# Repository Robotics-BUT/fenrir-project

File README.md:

# Fenrir Project - Universal Robotic Platform

The Fenrir Project is an open source of a multi purpose education robot dedicated for wide range of applications and usage in high-schools and universities.

The robot is based on Raspberry Pi 4 and Arduino Nano. The Raspberry Pi provides computational power, ROS2 support, WiFi connection and USB support. The Arduino Nano extends the PRi IOs and handles peripherals.

The development is currently still under development

## Robot Overview

### Robot visualization 

### Overview schematic

### Power supply schematic

### Wiring Overview

**Note**: The sensors numbering goes from left to right
 - Ultrasound 1 - left, Ultrasound 2 - center, Ultrasound 3 - right
 - Line sensor 1 - left, Line sensor 2 - right
 - Motor 1 - left, Motor 2 - right
 - Encoder 1 - left, Encoder 2 - right

| **Module A**       | **Pin**  | **Module B**        | **Pin**        | **Type**              | **Length** | **Note** |
|--------------------|----------|---------------------|----------------|-----------------------|------------|----------|
| Battery 1          | -        | PD Module           | -              | USB-C - USB-C         | 15cm       | -        |
| Battery 2          | -        | Raspberry Pi        | -              | USB-C - USB-C         | 15cm       | -        |
| Raspberry Pi       | -        | Camera              | -              | CSI Cable             | 10cm       | -        |
| Raspberry Pi       | 3v3      | GPS                 | VCC            | wire (blue)           | 10cm       | 3V3      |
| Raspberry Pi       | GND      | GPS                 | GND            | wire (black)          | 10cm       | GND      |
| Raspberry Pi       | Rx       | GPS                 | TxD            | wire (purple)         | 10cm       | UART     |
| Raspberry Pi       | 5V       | I2C Board           | 5V             | wire (red)            | 8cm        | 5V       |
| Raspberry Pi       | GND      | I2C Board           | GND            | wire (black)          | 8cm        | GND      |
| Raspberry Pi       | SCL      | I2C Board           | SCL            | wire (yellow)         | 8cm        | SCL      |
| Raspberry Pi       | SDA      | I2C Board           | SDA            | wire (green)          | 8cm        | SDA      |
| Raspberry Pi       | -        | LIDAR               | -              | USB-A - microUSB      | 10cm       | -        |
| I2C Board          | 5V       | LCD                 | VCC            | wire (red)            | 8cm        | 5V       |
| I2C Board          | GND      | LCD                 | GND            | wire (black)          | 8cm        | GND      |
| I2C Board          | SCL      | LCD                 | SCL            | wire (yellow)         | 8cm        | SCL      |
| I2C Board          | SDA      | LCD                 | SDA            | wire (green)          | 8cm        | SDA      |
| I2C Board          | 5V       | Arduino             | VCC            | wire (red)            | 15cm       | 5V       |
| I2C Board          | GND      | Arduino             | GND            | wire (black)          | 15cm       | GND      |
| I2C Board          | SCL      | Arduino             | SCL            | wire (yellow)         | 15cm       | SCL      |
| I2C Board          | SDA      | Arduino             | SDA            | wire (green)          | 15cm       | SDA      |
| Arduino            | US1      | Ultrasound 1        | Vcc            | wire (red)            | 10cm       | 5V       |
| Arduino            | US1      | Ultrasound 1        | GND            | wire (black)          | 10cm       | GND      |
| Arduino            | US1      | Ultrasound 1        | Echo/Trig      | wire (blue)           | 10cm       | signal   |
| Arduino            | US2      | Ultrasound 2        | Vcc            | wire (red)            | 10cm       | 5V       |
| Arduino            | US2      | Ultrasound 2        | GND            | wire (black)          | 10cm       | GND      |
| Arduino            | US2      | Ultrasound 2        | Echo/Trig      | wire (blue)           | 10cm       | signal   |
| Arduino            | US3      | Ultrasound 3        | Vcc            | wire (red)            | 15cm       | 5V       |
| Arduino            | US3      | Ultrasound 3        | GND            | wire (black)          | 15cm       | GND      |
| Arduino            | US3      | Ultrasound 3        | Echo/Trig      | wire (blue)           | 15cm       | signal   |
| Arduino            | Line1    | Line Sens. 1        | VCC            | wire (red)            | 15cm       | 5V       |
| Arduino            | Line1    | Line Sens. 1        | GND            | wire (black)          | 15cm       | GND      |
| Arduino            | Line1    | Line Sens. 1        | A0             | wire (blue)           | 15cm       | signal   |
| Arduino            | Line2    | Line Sens. 2        | VCC            | wire (red)            | 15cm       | 5V       |
| Arduino            | Line2    | Line Sens. 2        | GND            | wire (black)          | 15cm       | GND      |
| Arduino            | Line2    | Line Sens. 2        | A0             | wire (blue)           | 15cm       | signal   |
| Arduino            | 5V       | Encoder 1           | -              | wire (yellow)         | 20cm       | 5V       |
| Arduino            | GND      | Encoder 1           | -              | wire (brown)          | 20cm       | GND      |
| Arduino            | EN1A     | Encoder 1           | -              | wire (red)            | 20cm       | A        |
| Arduino            | EN1B     | Encoder 1           | -              | wire (orange)         | 20cm       | B        |
| Arduino            | 5V       | Encoder 2           | -              | wire (yellow)         | 20cm       | 5V       |
| Arduino            | GND      | Encoder 2           | -              | wire (brown)          | 20cm       | GND      |
| Arduino            | EN2A     | Encoder 2           | -              | wire (red)            | 20cm       | A        |
| Arduino            | EN2B     | Encoder 2           | -              | wire (orange)         | 20cm       | B        |
| Arduino            | GND      | PD Module           | OUT-           | wire (black)          | -          | -        |
| Arduino            | M1A      | H-Bridge            | IN3            | wire (yellow)         | 20cm       | PWM A+   |
| Arduino            | M1B      | H-Bridge            | IN4            | wire (green)          | 20cm       | PWM A-   |
| Arduino            | M2A      | H-Bridge            | IN1            | wire (yellow)         | 20cm       | PWM B+   |
| Arduino            | M2B      | H-Bridge            | IN2            | wire (green)          | 20cm       | PWM B-   |
| PD Module          | +        | H-Bridge            | +12V           | wire (orange)         | 15cm       | 12V      |
| PD Module          | -        | H-Bridge            | GND            | wire (black)          | 15cm       | GND      |
| H-Bridge           | OUT1+    | Motor 1             | -              | wire (green)          | 20cm       | +        |
| H-Bridge           | OUT1-    | Motor 1             | -              | wire (blue)           | 20cm       | -        |
| H-Bridge           | OUT2+    | Motor 2             | -              | wire (green)          | 20cm       | +        |
| H-Bridge           | OUT2-    | Motor 2             | -              | wire (blue)           | 20cm       | -        |

## Equipment

| Role                   | Component           | URL                                                                                                                                                                                                                                                                                             |
|------------------------|---------------------|-------------------------------------------------------------------------------------------------------------------------------------------------------------------------------------------------------------------------------------------------------------------------------------------------|
| Main Computer          | RPi                 | [link](https://cz.mouser.com/ProductDetail/Raspberry-Pi/SC01959?qs=T%252BzbugeAwjhNCW2QVhlotw%3D%3D)                                                                                                                                                                                            |
| Helper Microcontroller | Arduino Nano        | [link](https://www.laskakit.cz/arduino-nano-r3--atmega328p-klon--pripajene-piny/)                                                                                                                                                                                                               |
| 2x Battery             | Powerbank 10000 mAh | [link](https://www.alza.cz/alzapower-parade-power-delivery?dq=7177723)                                                                                                                                                                                                                          |
| Camera                 | RPi Camera v2       | [link](https://rpishop.cz/mipi-kamerove-moduly/329-raspberry-pi-kamera-modul-v2.html?utm_source=google&utm_medium=cpc&utm_campaign=CZ-PMax-Raspberry%20Pi&utm_id=19691368073&gad_source=1&gclid=Cj0KCQiAr7C6BhDRARIsAOUKifiiX4p72F4J8UeeA5uyoK2IDEEryKLRjE0e5gLhURTCTTf2cGW-ZpQaAr76EALw_wcB)   |
| GPS                    | NEO-7M module       | [link](https://dratek.cz/arduino/1733-gps-satelitni-urceni-polohy-neo-7m-modul.html?_gl=1*16f2vtr*_up*MQ..*_gs*MQ..&gclid=Cj0KCQiAr7C6BhDRARIsAOUKifhd7u9T5IjiCyc4w0n-WqehlzG5F2pNwJ4JP5M_eQDHW-daU_NkSKYaAn-_EALw_wcB)                                                                         |
| 2D LiDAR               | RPLiDAR A1M8        | [link](https://rpishop.cz/lidary/1631-rplidar-a1m8-360stupnovy-laserovy-scanner-kit-dosah-12m.html)                                                                                                                                                                                             |
| LCD                    | HD44780 20x4 I2C    | [link](https://dratek.cz/arduino/1421-eses-i2c-20x4-display-pro-jednodeskove-pocitace.html?_gl=1*16f2vtr*_up*MQ..*_gs*MQ..&gclid=Cj0KCQiAr7C6BhDRARIsAOUKifhd7u9T5IjiCyc4w0n-WqehlzG5F2pNwJ4JP5M_eQDHW-daU_NkSKYaAn-_EALw_wcB)                                                                  |
| 3x Ultrasound          | SRF-05              | [link](https://dratek.cz/arduino/1735-meric-vzdalenosti-ultrazvukovy-5pin-hy-srf05-pro-arduino.html?gad_source=1&gclid=Cj0KCQiAr7C6BhDRARIsAOUKifhd7u9T5IjiCyc4w0n-WqehlzG5F2pNwJ4JP5M_eQDHW-daU_NkSKYaAn-_EALw_wcB)                                                                            |
| 2x Line Sensor         | TCRT5000 module     | [link](https://www.laskakit.cz/arduino-infracerveny-senzor-sledovani-cary-s-lm393/)                                                                                                                                                                                                             |
| H Bridge               | L298N module        | [link](https://www.laskakit.cz/h-mustek-pro-krokovy-motor-l298n--dualni-motorovy-modul/)                                                                                                                                                                                                        |
| Motor with Encoder     | DG01D‐E             | [link](https://cz.mouser.com/ProductDetail/SparkFun/ROB-16413?qs=vmHwEFxEFR%2F20T1Ah9zr5w%3D%3D)                                                                                                                                                                                                |
| IMU                    | MPU6050             | [link](https://pajenicko.cz/gyroskop-akcelerometr-gy-521-s-mpu6050-i2c)                                                                                                                                                                                                                         |
| Barometer              | BME280              | [link](https://pajenicko.cz/senzor-na-mereni-teploty-vlhkosti-tlaku-bme280)                                                                                                                                                                                                                     |
| Real Time Clock        | DS3231              | [link](https://www.laskakit.cz/arduino-rtc-hodiny-realneho-casu-ds3231-at24c32/?utm_source=google&utm_medium=cpc&utm_campaign=1_PMax_%5BCZ%5D_Top_tROAS_540&utm_id=18587021915&gad_source=1&gclid=Cj0KCQiAr7C6BhDRARIsAOUKifg6UUgWdBpultpbW-joaJkbae34LBj8l6PJlVsHSvLgqnOoyetU0BsaAva-EALw_wcB) |
| ADC                    | ADS1115             | [link](https://pajenicko.cz/ad-prevodnik-ads1115-s-programovatelnym-zesilenim-16bit-4-kanaly-i2c-rozhrani)                                                                                                                                                                                      |
| UWB (not yet)          | DWM1000             | [link](https://www.laskakit.cz/decawave-dwm1000-lokalizacni-modul/)                                                                                                                                                                                                                             |
| DC/DC Step Up          | XL6009              | [link](https://www.laskakit.cz/step-up-boost-menic-s-xl6009--cervena/)                                                                                                                                                                                                                          |
| Power Delivery         | USB-C PD module     | [link](https://www.laskakit.cz/usb-c-pd-qc-prepinac-napajeciho-napeti/?utm_source=google&utm_medium=cpc&utm_campaign=1_PMax_%5BCZ%5D_Rest_tROAS_540&utm_id=20484705754&gad_source=1&gclid=Cj0KCQiAr7C6BhDRARIsAOUKifjczsmkcfvSqKLF3lqhT2G3EaCcH9kkrkxwS225di7C_nkNrmd77JoaAueFEALw_wcB)         |
| Switch                 |                     | [link](https://pajenicko.cz/kulaty-kolebkovy-spinac-se-zelenou-led-12v-20a)                                                                                                                                                                                                                     |

## Simulation

A Gazebo simulator of Fenrir lives in [`simulation/`](./simulation). It is a
digital twin of the robot: it exposes the same `/bpc_prp_robot/*` ROS 2 topics
as the real hardware, so course code runs unchanged in simulation and on the
robot.

It runs in a Docker container — no native Gazebo install needed. The line and
corridor worlds are ready; the maze world is in progress. See
[`simulation/README.md`](./simulation/README.md) for setup and how to run it.

## Acknowledgments

This work was created with the support of project RP182401001 under the PPSŘ 2025 program.

## Authors

Adam Ligocki - adam.ligocki@vut.cz

Petr Šopák - petr.sopak@vut.cz

Jakum Minařík

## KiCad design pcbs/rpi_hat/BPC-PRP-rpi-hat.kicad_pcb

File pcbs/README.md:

# Fenrir Project - PCBs

### RPi Ext Board

Schema

Render Top

Render Bot

### Arduino Board

Schema

Render Top

### I2C Board

Schema

Render Top

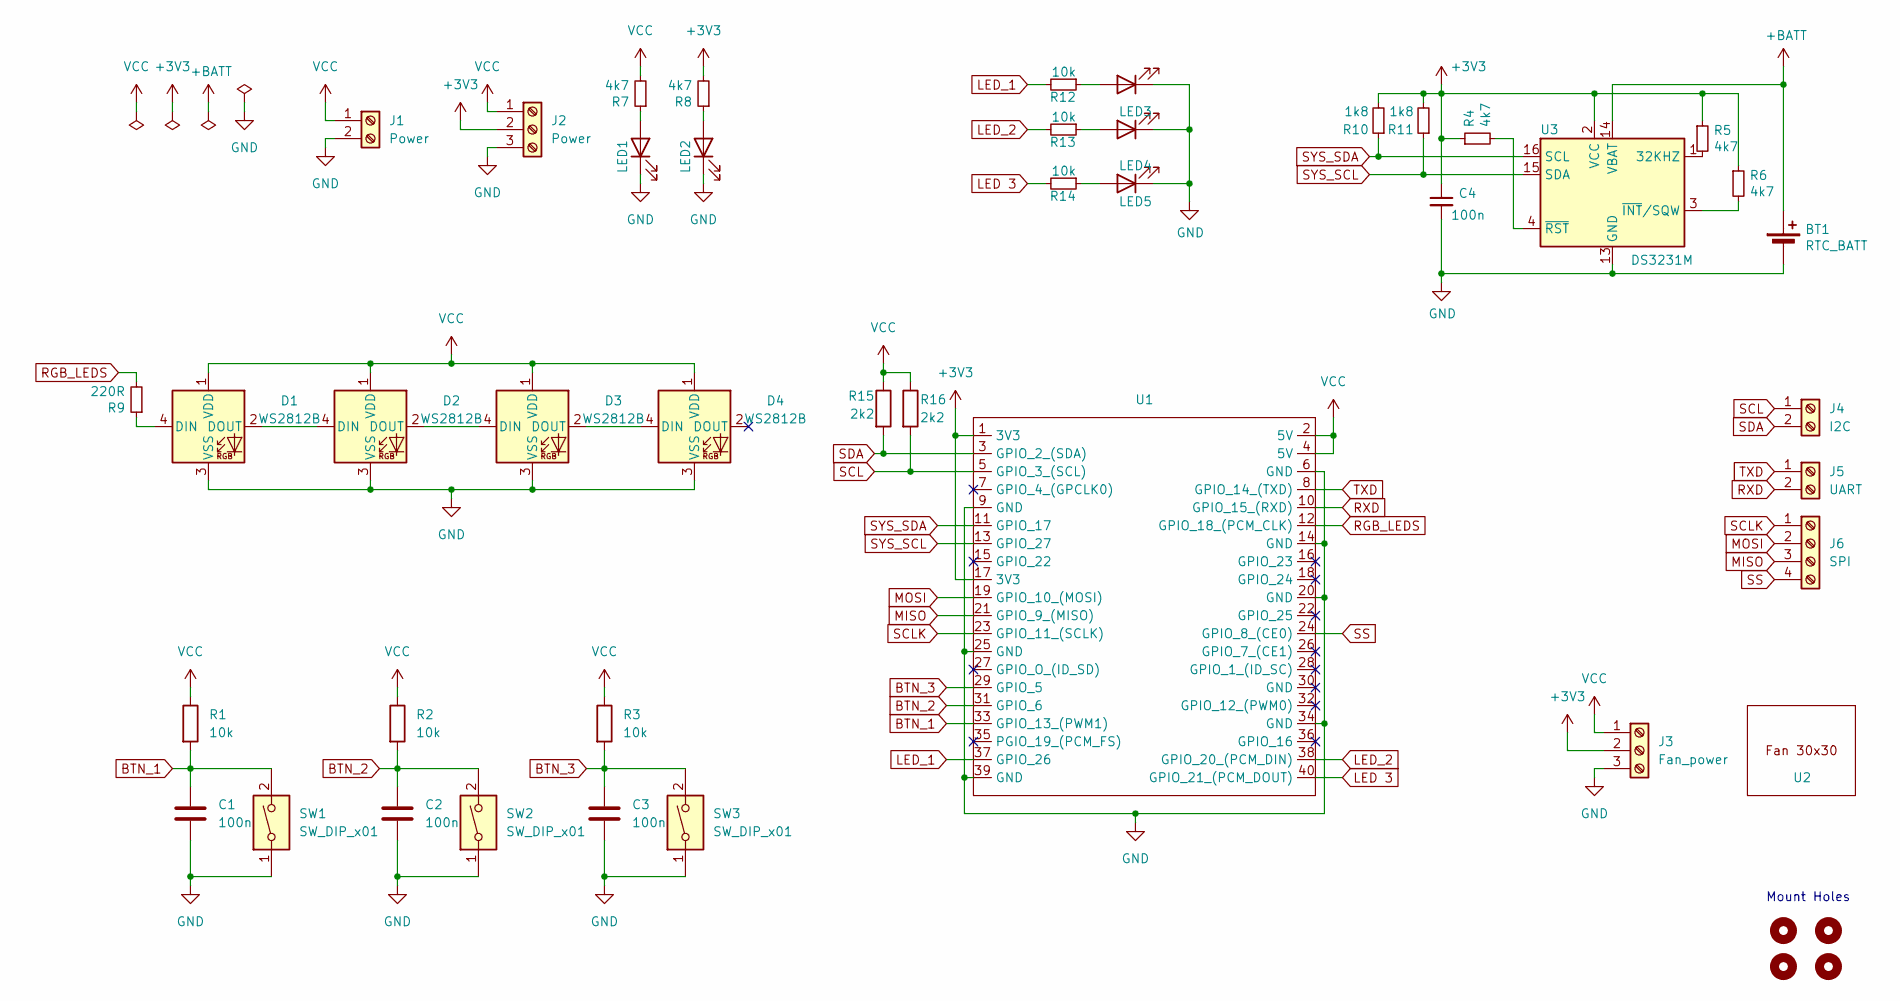
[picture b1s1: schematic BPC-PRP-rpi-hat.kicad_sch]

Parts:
BT1: RTC_BATT; BatteryHolder_Keystone_3000_1x12mm
C1, C2, C3, C4: 100n; C_1206_3216Metric
D1, D2, D3, D4: WS2812B; LED_WS2812B_PLCC4_5.0x5.0mm_P3.2mm
H1, H2, H3, H4: MountingHole; MountingHole_3.2mm_M3
J1: Power; TerminalBlock_RND_205-00001_1x02_P5.00mm_Horizontal
J2: Power; TerminalBlock_TE_282834-3_1x03_P2.54mm_Horizontal
J3: Fan_power; TerminalBlock_TE_282834-3_1x03_P2.54mm_Horizontal
J4: I2C; TerminalBlock_TE_282834-2_1x02_P2.54mm_Horizontal
J5: UART; TerminalBlock_TE_282834-2_1x02_P2.54mm_Horizontal
J6: SPI; TerminalBlock_TE_282834-4_1x04_P2.54mm_Horizontal
LED1, LED2, LED3, LED4, LED5: LED_1206_3216Metric
R1, R2, R3, R12, R13, R14: 10k; R_1206_3216Metric
R4, R5, R6, R7, R8: 4k7; R_1206_3216Metric
R9: 220R; R_1206_3216Metric
R10, R11: 1k8; R_1206_3216Metric
R15, R16: 2k2; R_1206_3216Metric
SW1, SW2, SW3: SW_DIP_x01; SW_PUSH_6mm_H5mm
U1: PinSocket_2x20_P2.54mm_Vertical
U2: FAN_30
U3: DS3231M; SOIC-16W_7.5x10.3mm_P1.27mm

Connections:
+3V3: C4.1, J2.2, J3.2, R4.1, R5.1, R6.1, R8.2, R10.2, R11.2, U1.1 (3V3), U1.17 (3V3), U3.2 (VCC)
+BATT: BT1.1 (+), U3.14 (VBAT)
BTN_1: C1.1, R1.2, SW1.2, U1.33 (GPIO_13_(PWM1))
BTN_2: C2.1, R2.2, SW2.2, U1.31 (GPIO_6)
BTN_3: C3.1, R3.2, SW3.2, U1.29 (GPIO_5)
GND: BT1.2 (-), C1.2, C2.2, C3.2, C4.2, D1.3 (VSS), D2.3 (VSS), D3.3 (VSS), D4.3 (VSS), J1.2, J2.3, J3.3, LED1.1 (K), LED2.1 (K), LED3.1 (K), LED4.1 (K), LED5.1 (K), SW1.1, SW2.1, SW3.1, U1.6 (GND), U1.9 (GND), U1.14 (GND), U1.20 (GND), U1.25 (GND), U1.34 (GND), U1.39 (GND), U3.5 (GND), U3.6 (GND), U3.7 (GND), U3.8 (GND), U3.9 (GND), U3.10 (GND), U3.11 (GND), U3.12 (GND), U3.13 (GND)
LED 3: R14.2, U1.40 (GPIO_21_(PCM_DOUT))
LED_1: R12.2, U1.37 (GPIO_26)
LED_2: R13.2, U1.38 (GPIO_20_(PCM_DIN))
MISO: J6.3, U1.21 (GPIO_9_(MISO))
MOSI: J6.2, U1.19 (GPIO_10_(MOSI))
unnamed: D1.4 (DIN), R9.1
unnamed: D1.2 (DOUT), D2.4 (DIN)
unnamed: D2.2 (DOUT), D3.4 (DIN)
unnamed: D3.2 (DOUT), D4.4 (DIN)
unnamed: LED1.2 (A), R7.1
unnamed: LED2.2 (A), R8.1
unnamed: LED3.2 (A), R12.1
unnamed: LED4.2 (A), R13.1
unnamed: LED5.2 (A), R14.1
unnamed: R5.2, U3.1 (32KHZ)
unnamed: R6.2, U3.3 (~INT/SQW)
unnamed: R4.2, U3.4 (~RST)
RGB_LEDS: R9.2, U1.12 (GPIO_18_(PCM_CLK))
RXD: J5.2, U1.10 (GPIO_15_(RXD))
SCL: J4.1, R16.2, U1.5 (GPIO_3_(SCL))
SCLK: J6.1, U1.23 (GPIO_11_(SCLK))
SDA: J4.2, R15.2, U1.3 (GPIO_2_(SDA))
SS: J6.4, U1.24 (GPIO_8_(CE0))
SYS_SCL: R11.1, U1.13 (GPIO_27), U3.15 (SDA)
SYS_SDA: R10.1, U1.11 (GPIO_17), U3.16 (SCL)
TXD: J5.1, U1.8 (GPIO_14_(TXD))
VCC: D1.1 (VDD), D2.1 (VDD), D3.1 (VDD), D4.1 (VDD), J1.1, J2.1, J3.1, R1.1, R2.1, R3.1, R7.2, R15.1, R16.1, U1.2 (5V), U1.4 (5V)

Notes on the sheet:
Mount Holes

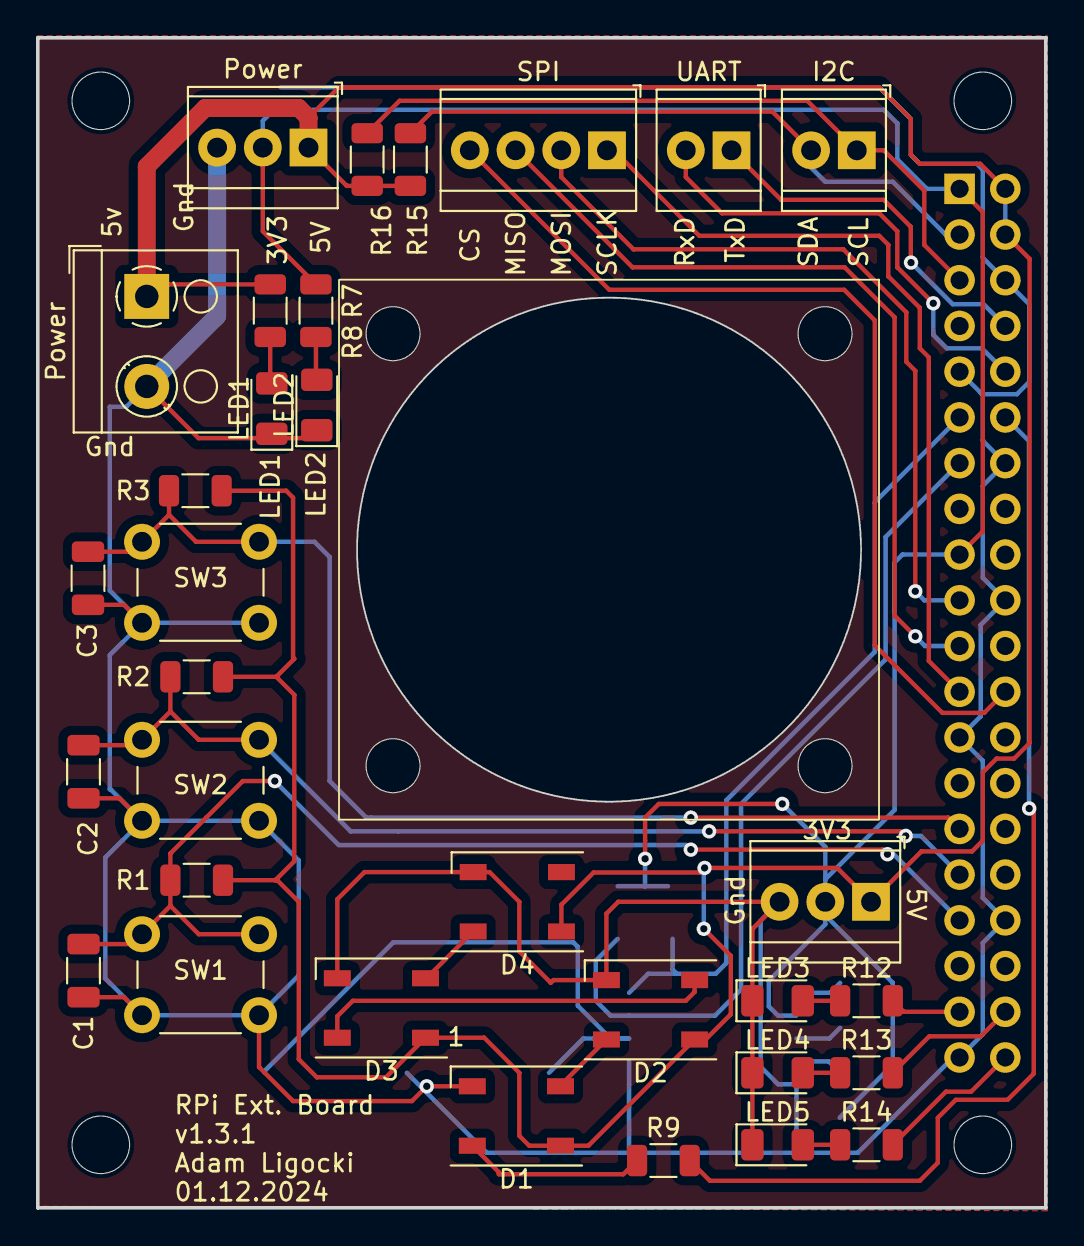
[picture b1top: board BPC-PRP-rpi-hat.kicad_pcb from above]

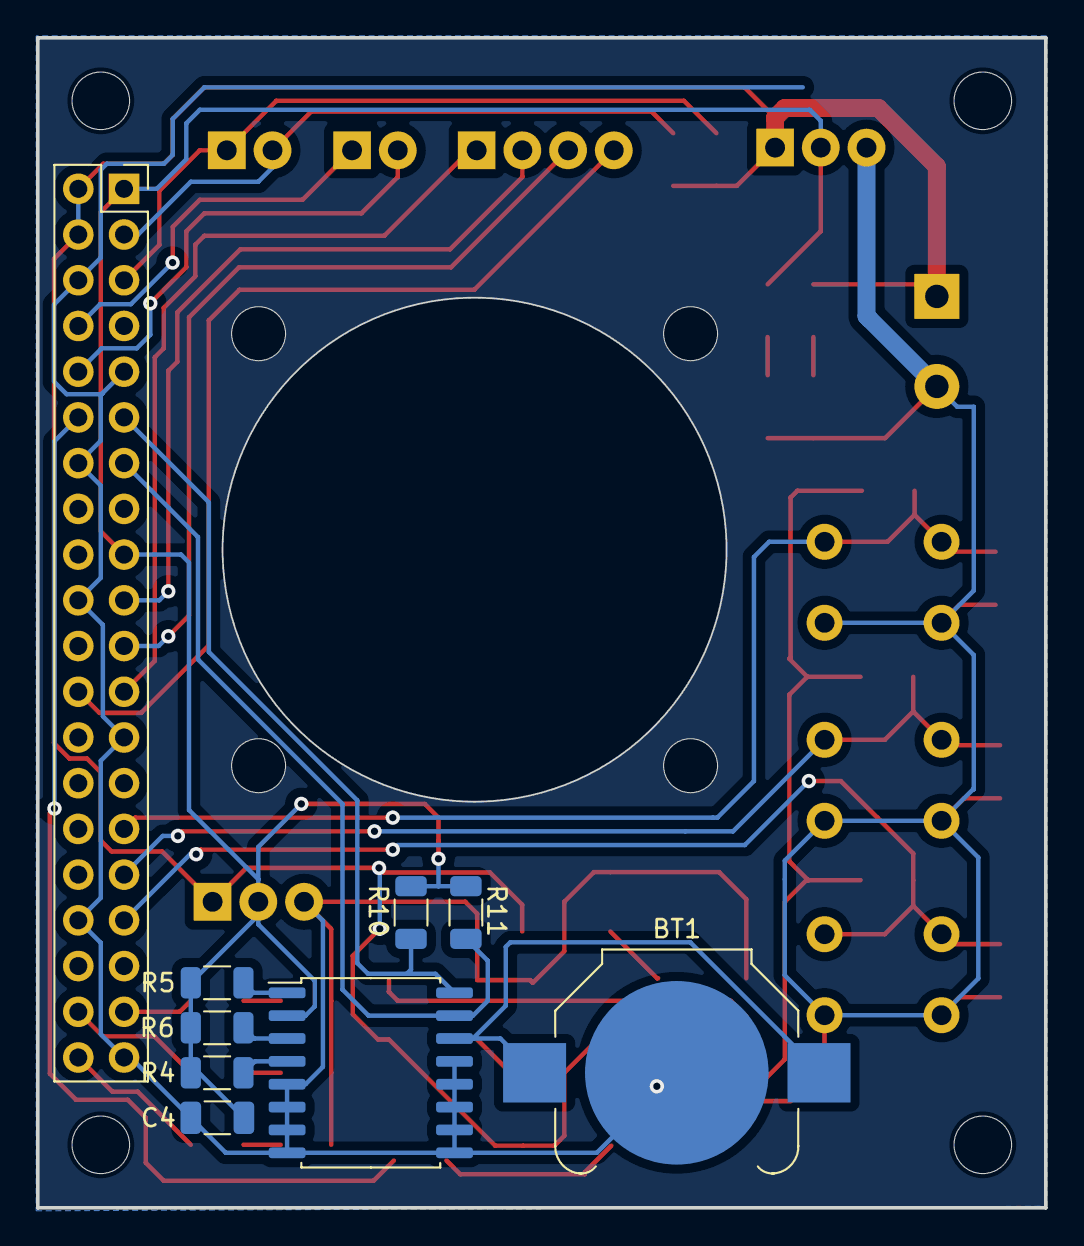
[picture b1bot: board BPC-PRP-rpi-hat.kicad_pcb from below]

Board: 2 copper layers, 56.0 x 65.0 mm, 46 parts (9 on the bottom side), 33 nets.

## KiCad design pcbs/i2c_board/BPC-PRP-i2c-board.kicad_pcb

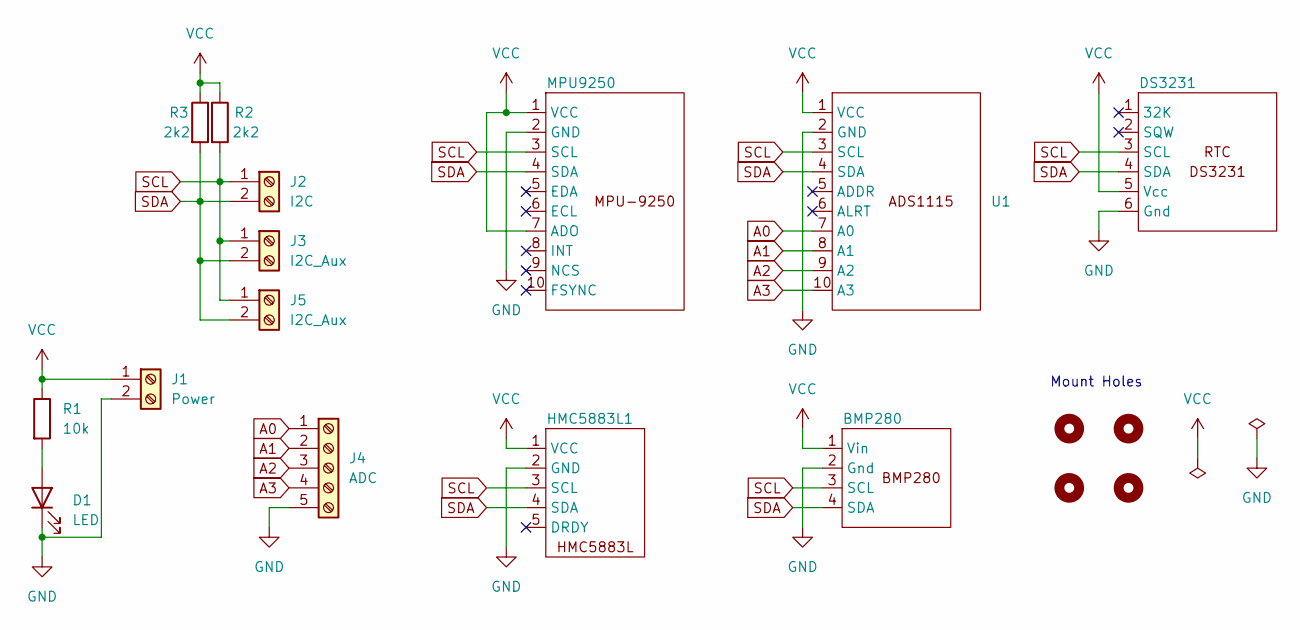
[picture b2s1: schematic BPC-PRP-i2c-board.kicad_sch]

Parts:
BMP280: bmp280
D1: LED; LED_1206_3216Metric
DS3231: rtc_ds3231
H1, H2, H3, H4: MountingHole; MountingHole_3.2mm_M3
HMC5883L1: HMC5883L
J1: Power; TerminalBlock_TE_282834-2_1x02_P2.54mm_Horizontal
J2: I2C; TerminalBlock_TE_282834-2_1x02_P2.54mm_Horizontal
J3, J5: I2C_Aux; TerminalBlock_TE_282834-2_1x02_P2.54mm_Horizontal
J4: ADC; TerminalBlock_TE_282834-5_1x05_P2.54mm_Horizontal
MPU9250: MPU-9250
R1: 10k; R_1206_3216Metric
R2, R3: 2k2; R_1206_3216Metric
U1: ADS1115

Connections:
A0: J4.1, U1.7 (A0)
A1: J4.2, U1.8 (A1)
A2: J4.3, U1.9 (A2)
A3: J4.4, U1.10 (A3)
GND: BMP280.2 (Gnd), D1.1 (K), DS3231.6 (Gnd), HMC5883L1.2 (GND), J1.2, J4.5, MPU9250.2 (GND), U1.2 (GND)
unnamed: D1.2 (A), R1.2
SCL: BMP280.3 (SCL), DS3231.3 (SCL), HMC5883L1.3 (SCL), J2.1, J3.1, J5.1, MPU9250.3 (SCL), R2.2, U1.3 (SCL)
SDA: BMP280.4 (SDA), DS3231.4 (SDA), HMC5883L1.4 (SDA), J2.2, J3.2, J5.2, MPU9250.4 (SDA), R3.2, U1.4 (SDA)
VCC: BMP280.1 (Vin), DS3231.5 (Vcc), HMC5883L1.1 (VCC), J1.1, MPU9250.1 (VCC), MPU9250.7 (ADO), R1.1, R2.1, R3.1, U1.1 (VCC)

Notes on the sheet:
Mount Holes

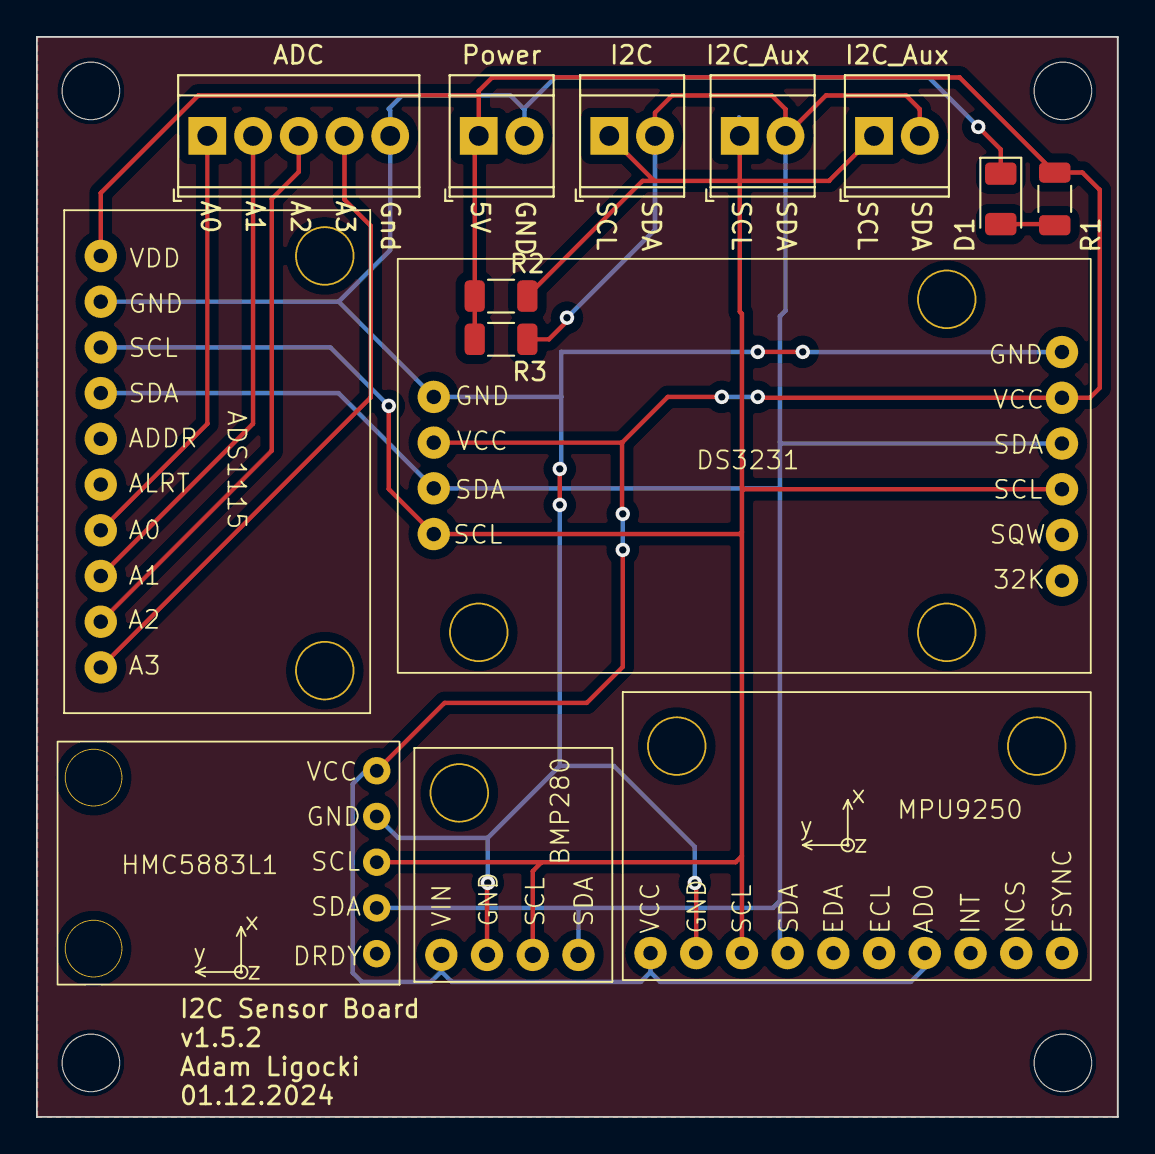
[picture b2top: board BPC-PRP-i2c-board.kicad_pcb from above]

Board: 2 copper layers, 60.0 x 60.0 mm, 18 parts (0 on the bottom side), 9 nets.

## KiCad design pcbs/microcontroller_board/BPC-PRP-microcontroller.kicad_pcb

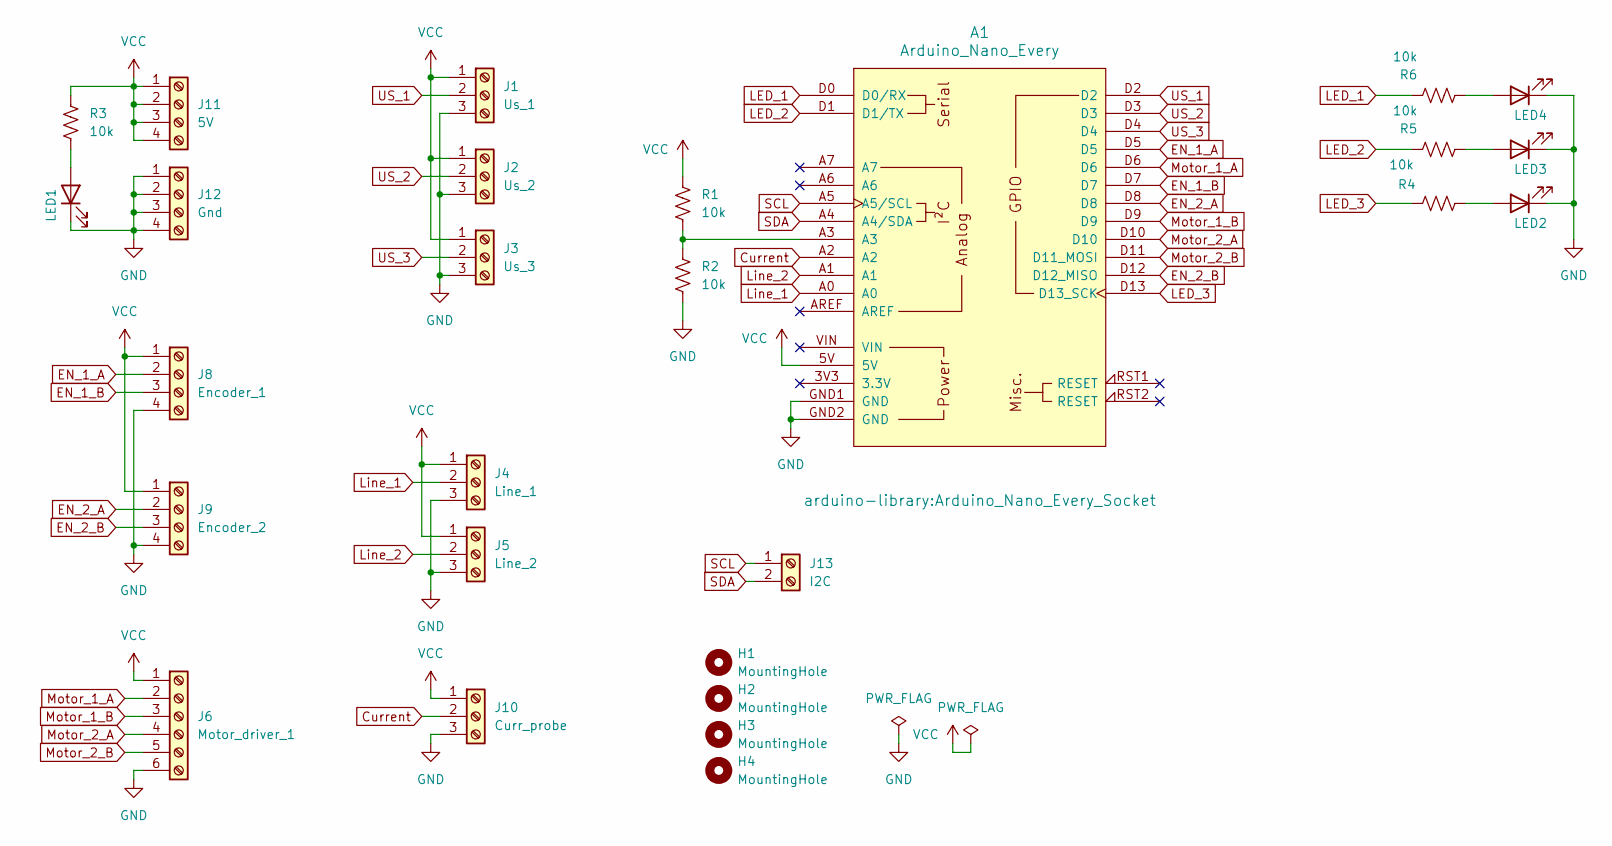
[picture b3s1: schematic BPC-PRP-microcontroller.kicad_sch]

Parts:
A1: Arduino_Nano_Every; Arduino_Nano_Every_Socket
H1, H2, H3, H4: MountingHole; MountingHole_3.2mm_M3
J1: Us_1; TerminalBlock_TE_282834-3_1x03_P2.54mm_Horizontal
J2: Us_2; TerminalBlock_TE_282834-3_1x03_P2.54mm_Horizontal
J3: Us_3; TerminalBlock_TE_282834-3_1x03_P2.54mm_Horizontal
J4: Line_1; TerminalBlock_TE_282834-3_1x03_P2.54mm_Horizontal
J5: Line_2; TerminalBlock_TE_282834-3_1x03_P2.54mm_Horizontal
J6: Motor_driver_1; TerminalBlock_TE_282834-6_1x06_P2.54mm_Horizontal
J8: Encoder_1; TerminalBlock_TE_282834-4_1x04_P2.54mm_Horizontal
J9: Encoder_2; TerminalBlock_TE_282834-4_1x04_P2.54mm_Horizontal
J10: Curr_probe; TerminalBlock_TE_282834-3_1x03_P2.54mm_Horizontal
J11: 5V; TerminalBlock_TE_282834-4_1x04_P2.54mm_Horizontal
J12: Gnd; TerminalBlock_TE_282834-4_1x04_P2.54mm_Horizontal
J13: I2C; TerminalBlock_TE_282834-2_1x02_P2.54mm_Horizontal
LED1, LED2, LED3, LED4: LED_1206_3216Metric
R1, R2, R3, R4, R5, R6: 10k; R_1206_3216Metric

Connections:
Current: A1.A2, J10.2
EN_1_A: A1.D5, J8.2
EN_1_B: A1.D7, J8.3
EN_2_A: A1.D8, J9.2
EN_2_B: A1.D12 (D12_MISO), J9.3
GND: A1.GND1 (GND), A1.GND2 (GND), J1.3, J2.3, J3.3, J4.3, J5.3, J6.6, J8.4, J9.4, J10.3, J12.1, J12.2, J12.3, J12.4, LED1.1 (K), LED2.1 (K), LED3.1 (K), LED4.1 (K), R2.2
LED_1: A1.D0 (D0/RX), R6.1
LED_2: A1.D1 (D1/TX), R5.1
LED_3: A1.D13 (D13_SCK), R4.1
Line_1: A1.A0, J4.2
Line_2: A1.A1, J5.2
Motor_1_A: A1.D6, J6.2
Motor_1_B: A1.D9, J6.3
Motor_2_A: A1.D10, J6.4
Motor_2_B: A1.D11 (D11_MOSI), J6.5
unnamed: A1.A3, R1.2, R2.1
unnamed: LED1.2 (A), R3.2
unnamed: LED2.2 (A), R4.2
unnamed: LED3.2 (A), R5.2
unnamed: LED4.2 (A), R6.2
SCL: A1.A5 (A5/SCL), J13.1
SDA: A1.A4 (A4/SDA), J13.2
US_1: A1.D2, J1.2
US_2: A1.D3, J2.2
US_3: A1.D4, J3.2
VCC: A1.5V, J1.1, J2.1, J3.1, J4.1, J5.1, J6.1, J8.1, J9.1, J10.1, J11.1, J11.2, J11.3, J11.4, R1.1, R3.1

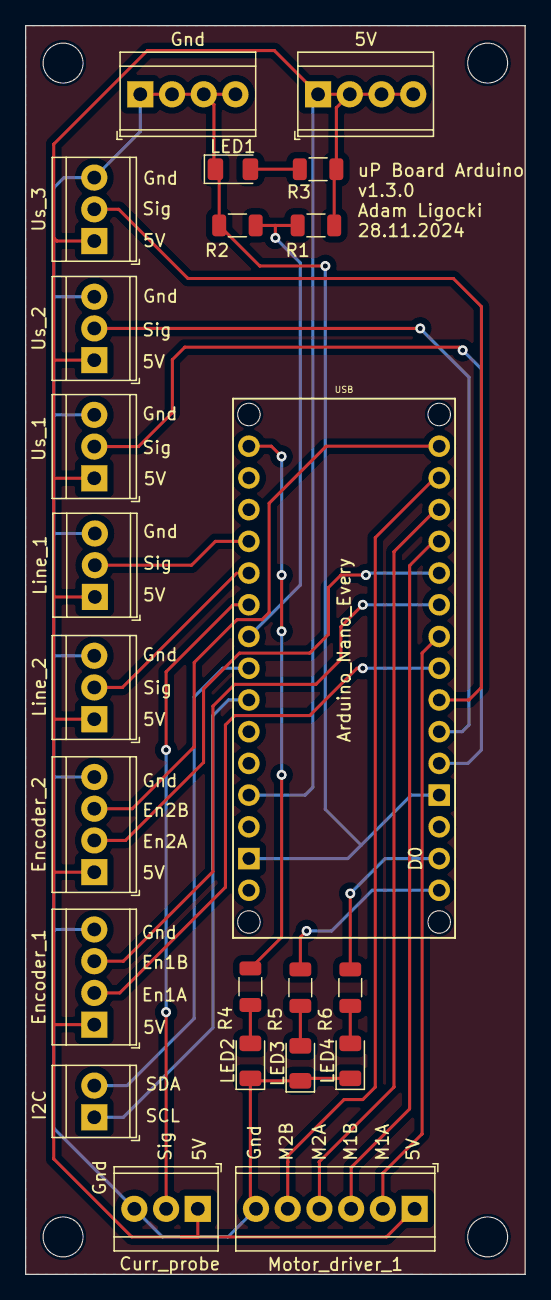
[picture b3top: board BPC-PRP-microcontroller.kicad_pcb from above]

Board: 2 copper layers, 40.0 x 100.0 mm, 27 parts (0 on the bottom side), 26 nets.

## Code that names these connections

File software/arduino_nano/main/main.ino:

#include <Wire.h>
#include <Encoder.h>

#define ARDUINO_BOARD

#ifdef ARDUINO_BOARD
#define US_0 2
#define US_1 3
#define US_2 4
#define EN_0_A 5
#define EN_0_B 7
#define EN_1_A 8
#define EN_1_B 12
#define MOT_0_A 6
#define MOT_0_B 9
#define MOT_1_A 10
#define MOT_1_B 11
#define LINE_0 A0
#define LINE_1 A1
#define CURR A2
#define I2C_SDA 
#define I2C_SCL 
#endif


#define MOT_IDLE 127
#define SLAVE_ADDRESS 0x50
#define EEPROM_SIZE 21
#define MOTOR_PULSES_PER_ROT 576

enum US_STATE {
  START = 0,
  WAIT = 1,
  DONE = 2,
};

union EncoderU {
  int32_t value = 0;
  uint8_t bytes[4];
};

union LineU {
  uint16_t value = 0;
  uint8_t bytes[2];
};

union CurrentU {
  uint16_t value = 0;
  uint8_t bytes[2];
};


/*
 * Data Space
 * 
 * 0 - US_0 dist [cm] (8b)
 * 1 - US_1 dist [cm] (8b)
 * 2 - US_2 dist [cm] (8b)
 * 3 - encoder_A [-] (32b)
 * 4   ...
 * 5   ...
 * 6   ...
 * 7 - encoder_B [1] (32b)
 * 8   ...
 * 9   ...
 * 10  ...
 * 11 - current probe [-] (2b)
 * 12  ...
 * 13 - line_sens_0 [-] (2b)
 * 14  ...
 * 15 - line_sens_1 [-] (2b)
 * 16  ...
 * 17 - req_motor_0_speed [-] (1b) (0 - full back, 127 - stop, 255 - full forward) / 127 - 0m/s, 128 - 0.01m/s, 255 - 1.28m/s, 0 - -1.27m/s
 * 18 - req_motor_1_speed [-] (1b) (0 - full back, 127 - stop, 255 - full forward)
 * 19 - reserver
 */
 
uint8_t eeprom[EEPROM_SIZE];
uint8_t address = 0;
uint8_t i2c_write_val = 0;

uint8_t us_pins[3] = {US_0, US_1, US_2};
uint8_t us_state = 0;
unsigned long us_start_time = 0;
uint8_t us_index = 0;
const byte us_eeprom_offset = 0;

 
Encoder enc_0(EN_0_A, EN_0_B);
Encoder enc_1(EN_1_A, EN_1_B);
EncoderU en_0, en_1;

LineU line_0;
LineU line_1;
CurrentU curr;

uint8_t l_motor_pwm = 127;
uint8_t r_motor_pwm = 127;

void setup() {

    Serial.begin (115200);
    while (!Serial) {}

    Wire.begin(SLAVE_ADDRESS);
    Wire.onRequest(requestEvent);
    Wire.onReceive(receiveEvent);
    for (int i = 0; i < EEPROM_SIZE; i++) {
        eeprom[i] = 0;
    }
    eeprom[17] = 127; // motors stop
    eeprom[18] = 127;
    motor_task();

    Serial.print("Start\n");
}


void loop() {    
    ultrasound_task();
    encoder_task();
    line_task();
    current_task();
    eeprom_task();
    motor_control_task();
    motor_task();
    
    // delay(1);
    delayMicroseconds(100);
}

// Tasks

void ultrasound_task() {

  uint8_t i = us_index;

  switch (us_state) {
  case US_STATE::START: 

    // Serial.println("S");
    pinMode(us_pins[i], OUTPUT);
    digitalWrite(us_pins[i], LOW);
    delayMicroseconds(2);
    
    digitalWrite(us_pins[i], HIGH);
    delayMicroseconds(10);
    
    digitalWrite(us_pins[i], LOW);
    us_start_time = micros();
    pinMode(us_pins[i], INPUT);
    attachInterrupt(digitalPinToInterrupt(us_pins[i]), on_us, CHANGE);
    us_state = US_STATE::WAIT;
    break;

  case US_STATE::WAIT: 
    // Serial.println("W");
    if (micros() - us_start_time > 10000) { // timeout (about 1m max dist)
      detachInterrupt(digitalPinToInterrupt(us_pins[i]));
      eeprom[us_eeprom_offset + i] = 255;
      us_state = US_STATE::DONE;  
    }
    break;

  case US_STATE::DONE:
    // Serial.println("D");
    us_state = US_STATE::START;
    us_index = (us_index + 1) % 3;
    break;
  }
}

void encoder_task() {
  en_0.value = enc_0.read();
  en_1.value = enc_1.read();
}

void line_task() {
  line_0.value = analogRead(LINE_0);
  line_1.value = analogRead(LINE_1);
}

void current_task() {
  curr.value = analogRead(CURR);
}


void eeprom_task() {
  noInterrupts();

  eeprom[3] = en_0.bytes[3];
  eeprom[4] = en_0.bytes[2];
  eeprom[5] = en_0.bytes[1];
  eeprom[6] = en_0.bytes[0];

  eeprom[7] = en_1.bytes[3];
  eeprom[8] = en_1.bytes[2];
  eeprom[9] = en_1.bytes[1];
  eeprom[10] = en_1.bytes[0];
  
  eeprom[11] = curr.bytes[1];
  eeprom[12] = curr.bytes[0];

  eeprom[13] = line_0.bytes[1];
  eeprom[14] = line_0.bytes[0];

  eeprom[15] = line_1.bytes[1];
  eeprom[16] = line_1.bytes[0];

  interrupts();
}

void motor_task() {
  if (l_motor_pwm < MOT_IDLE) {
        analogWrite(MOT_0_A, 0);
        analogWrite(MOT_0_B, (MOT_IDLE - l_motor_pwm) * 2);
  } else if (l_motor_pwm == MOT_IDLE) {
      analogWrite(MOT_0_A, 0);
      analogWrite(MOT_0_B, 0);
  } else {
      analogWrite(MOT_0_A, (l_motor_pwm - 127) * 2);
      analogWrite(MOT_0_B, 0);
  }

  if (r_motor_pwm < MOT_IDLE) {
      analogWrite(MOT_1_A, 0);
      analogWrite(MOT_1_B, (MOT_IDLE - r_motor_pwm) * 2);
  } else if (r_motor_pwm == MOT_IDLE) {
      analogWrite(MOT_1_A, 0);
      analogWrite(MOT_1_B, 0);
  } else {
      analogWrite(MOT_1_A, (r_motor_pwm - MOT_IDLE) * 2);
      analogWrite(MOT_1_B, 0);
  }
}

class LowPass {
  public:
    LowPass(float coef) : coef_{coef} {}

    float step (float x) {
      val_ = coef_ * val_ + (1.0 - coef_) * x;
      return val_;
    }

  private:
    float val_ = 0;
    float coef_ = 0.0;
};

class Speeder {
  public:
  float step(int32_t encoder, float dt) {
    if (first_) {
      first_ = false;
      last_encoder_ = encoder;
      return 0.0;
    }
    int32_t enc_diff = ((encoder - last_encoder_));
    last_encoder_ = encoder;
    return -((float)(enc_diff)) / dt / MOTOR_PULSES_PER_ROT * 6.28 * 0.033;
  }
  private:
  bool first_ = true;
  float last_encoder_ = 0;
};

class PID {
  public: 
  PID(float p, float i, float d) {
    kp = p;
    ki = i;
    kd = d;
  }

  int8_t step (float speed, float setpoint, float dt) {

    float err = setpoint - speed;

    last_err = err;

    integral += err * dt;
    if (integral * ki > max_output) {
      integral = max_output / ki;
    }
    else if (integral * ki < -max_output) {
      integral = -max_output / ki;
    }

    float deriv = (err - last_err) / dt;
    float output = kp * err + ki * integral + kd * deriv;
    integral *= 0.99;
    return constrain((int)output, -max_output, max_output);
  }
  private:

  float kp = 0.0;
  float ki = 0.0;
  float kd = 0.0;
  float integral = 0.0;
  float last_err = 0.0;
  float max_output = 127;
};

class MotorPipeline {
  
  static constexpr float KP = 4000.0;
  static constexpr float KI = KP * 0.5f; //1000.0;
  static constexpr float KD = KP * 0.25f; //500.0;

  public:
  MotorPipeline() : pid_{KP, KI, KD}, low_pass_(0.9) {}

  float step(int32_t enc, float setpoint, float dt) {
    float spd = speeder_.step(enc, dt);
    float spd_lp = low_pass_.step(spd);
    // Serial.print(setpoint);
    // Serial.print(", ");
    // Serial.print(spd);
    // Serial.print(", ");
    // Serial.print(spd_lp);
    // Serial.print("\n");
    // printf("%f, %f, %f\n", setpoint, spd, spd_lp);
    float output = pid_.step(spd_lp, setpoint, dt);
    return output;
  }

  private:
  Speeder speeder_;
  LowPass low_pass_;
  PID pid_;
};


MotorPipeline mot_pipeline_l;
MotorPipeline mot_pipeline_r;

void motor_control_task() {

  static unsigned long last_time = millis();
  float setpoint_l = float(eeprom[17] - 127) / 100.0; //0.5 * sin(millis()/1000.0); 
  float setpoint_r = float(eeprom[18] - 127) / 100.0; 
  
  unsigned long current_time = millis();
  unsigned long elapsed_time = current_time - last_time;

  if (elapsed_time >= 1) {
    float dt = (float) elapsed_time / 1000.0;

    l_motor_pwm = 127 + mot_pipeline_l.step(en_0.value, -setpoint_l, dt);
    r_motor_pwm = 127 + mot_pipeline_r.step(en_1.value, setpoint_r, dt);
    last_time = current_time;
  }
}


// Interrupts

void on_us() {
  uint8_t i = us_index;
  if(digitalRead(us_pins[i]) == HIGH) {
    us_start_time = micros();
  } else if (digitalRead(us_pins[i]) == LOW) {
    uint8_t distance = (micros() - us_start_time) / 58;
    eeprom[us_eeprom_offset + i] = distance;
    detachInterrupt(digitalPinToInterrupt(us_pins[i]));
      us_state = US_STATE::DONE;  
  }
}


uint8_t i2c_val = 0;

void requestEvent() {
    Wire.write(eeprom[address]);
}


void receiveEvent(int bytes) {
    if (bytes == 1) {
        address = Wire.read();
    } else if (bytes == 2) {
        address = Wire.read();
        eeprom[address] = Wire.read();
    }
}

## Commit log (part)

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2024-11-25 first readme
2024-11-25 updated images
2024-11-25 updated images - hotfix
2024-11-25 add license
2024-11-25 added 3d print components
2024-11-25 added pcbs
2024-11-25 added overall schematics
2024-11-25 updated logo
2024-11-25 updated readme and overview schematics
2024-11-26 add arduino firmware
2024-11-26 add power supply schematic
2024-11-28 updated rpi ext board
2024-11-28 updated arduino board, add leds
2024-11-28 minor update i2c board, added pdbs schematics and renders
2024-11-28 added wheel.stl for 3d print
2024-12-01 add wiring diagram
2024-12-01 add i2c pullups for rpi ext and i2c board
2024-12-01 added draw io wirign schema
2024-12-02 updated srf05 holder, whee, added ball and pillar
2024-12-03 Add mdbook
2024-12-03 deploy: 4a336ef4fbffbd4892ea28003ddafd57dfd0acc7
2024-12-03 hotfix mdbook
2024-12-03 deploy: fe9c17568b525ea795d9cf78dc0eea5d07ef99b2
2024-12-03 add arduino tutorial
2024-12-03 deploy: 772fd85ce7f0d7503dfbdcde1e205ccc132ff559
2025-01-05 add wiring table
2025-01-05 update wiring picture
2025-01-05 update wiring schema drawio file
2025-01-12 added rpi software
2025-01-12 removed redundant build files
2025-01-13 updated arduino code
2025-01-28 Repair intendation
2025-01-28 Installation scripts
2025-01-28 Change services, mostly paths
2025-01-28 Tested on clean system
2025-01-28 Change legacy mode for camera
2025-01-31 Guide and test on clean sd card
2025-02-03 Spelling check
2025-02-03 Rpi install (#1)
    * Repair intendation
    * Installation scripts
    * Change services, mostly paths
    * Tested on clean system
    * Change legacy mode for camera
    * Guide and test on clean sd card
2025-02-03 deploy: f39b8b81aa648e7b6aa7750726b767b0fa8114ae
2025-02-05 add assembly documentation
2025-02-05 deploy: b32c804476d3648d762cadddd00725b47f554fad
2025-02-08 updated arduino sw
2025-02-17 updated imu
2025-03-19 Script to reduce startup time
2025-03-19 Added docs for faster boot configuration
2025-03-19 deploy: 56526d018df289b9af726164fa741eb20590085f
2025-10-09 updated book. work in progress
2025-10-09 mdbook hotfix
2025-10-09 deploy: 345499778fbfb0c0acada2148277d7597beed9ab
2025-10-09 update rplidar lib
2025-10-09 deploy: 8744e9b2f380c481394fb5963a3cb19a08991b7a
2025-10-09 sw chapter introduced
2025-10-09 deploy: 6ae57c39e9c4d8904b03d71b992625dc586ef147
2025-10-09 Title page updated
2025-10-09 deploy: 61d555a48f7d15f2b732c7e96c4e1bdb81f28e1e
2025-10-13 updated book. added sw description and hw bom, modules and wiring
2025-10-13 deploy: b2298da83181d34413b5533b3a15e039aea883dc
2025-10-13 updated chapter names
2025-10-13 deploy: 5b5df19f69a3a412cdbe865cb5fef0824e9e5160
2025-10-13 deploy: 01805a9bc7ab7766008ed6b0507c0afd6db83d27
2025-10-13 deploy: 827747b35de1bcf4ddc6bb2872d1ee9a19eb934e
2025-10-14 Intro hotfixes
2025-10-14 deploy: 7523dd05c0fd638708ff32a61843c69f63ddfe5a
2025-10-14 hardware intro hotfix
2025-10-14 deploy: f86e6548de95add1ba53676d715b00efa5ea2ce8
2025-10-14 3D_print hotfix
2025-10-14 deploy: 8701eb4418f3c0c8111d46cc281fb547b3eab31c
2025-10-14 modules_hotfix
2025-10-14 deploy: f0609b665d8adce5ccc3ca265ecc64aef48cfc09
2025-10-14 custom_pcbs hotfix
2025-10-14 deploy: c9a08f8d64d9041688ae44a8f5cccee1ff60a902
2025-10-14 wiring hotfix
2025-10-14 deploy: 460d7f242adc7587416baa26314140622ac502c2
2025-10-14 bom hotfix
2025-10-14 deploy: 4a7c87526ab97d80d7712786b8eec8d73a510d0b
2025-10-14 rpi_sw.md
2025-10-14 deploy: 3039dfad276a3518ae05c7a7b87240f059ca3857
2025-10-14 arduino_fw
2025-10-14 deploy: fdc0f2c28de8a9d118ba8db6f4d8e8211f452cc8
2025-10-14 rpi hotfix
2025-10-14 deploy: 2551b3f0d3e10813cc167ed59074bb7a0826f373
2025-10-14 arduino text hotfix
2025-10-14 deploy: cd957a312edc25db8ad836b08f1c4d3bf44c8ee2
2025-10-14 wirings
2025-10-14 deploy: e0f0f379acd168347a47d20ac2484d772fb99ca4
2025-10-14 added missing photos
2025-10-14 deploy: 6aae03548df7434008292925fec2408935213e14
2025-10-14 deploy: 0ccea8c862c81fcfa12cf519e9bc84c7c20e6293
